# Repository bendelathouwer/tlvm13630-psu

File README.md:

# circuit explenation 

----------------------------------------------------------------------------------------------------------------------------------------

Now the input circuitry and output circuitry,   the input and output capasitors, the datasheet demands ceramic capasitors with a dielectricum of X7R or better.
Why ceramic capacitors you may ask? because there ESR(equivalent series resitance) is low. which in turn means  lower ripel , control loop is stabel, better transient response and the losses are lower.

For the output circuitry we especialy want that to be suuper stable , why you may ask? Let me show you.

As you can see from this block diagram of the chip  the feedback circuitry is connected (via resistors) to the output. So as you can guess and see any oscilation will upset the comperator which in turn will pass and upset the control circuitry

----------------------------------------------------------------------------------------------------------------------------------

Now we will explain the controll pins a bit.
The first pin we encounter is the Enable pin, which we can use in one of three ways/
The first way is to just tie it to the input voltage , when we do this the convertor will start working whenever a input voltage is present.
The next posibility is to connect an external signal to the enable pin , this can be a microcontroller for example or this can be the power good signal of a upstream convertor.
This is done for when powersequencing is needed , an example of power sequencing can be seen below.

The next and last posebility is to add a voltage devider so we enable the UVLO(Under Voltage Lock Out). This will disable the convertor until a certain voltage is reached or disable the convertor if a voltage dips below a treshold.
This is handy when we are using batterys for example 

The next pin will be the Rt pin ,this pin sets the internal oscilator via a resistor. We need to be careful to choose this resistor. The higher the frequency the more emc and efficency  will become a problem BUT the components can be smaller.
The lower the frequency the lower emc will be and the efficency will be higher BUT the components will be bigger 

The next pin is the VCC pin which comes from the external regulator. Now the datasheet mentions multiple times that there shoudn't be any load connected to the VCC pin BUT in the application schematic in the datasheet it show a load (albeit a pull up).
The EVM schematic shows no load even no pullup connected, so for me it is a mistery if you should or should not connect a load to it.

Next pin is the power good pin , this pin is an open drain pin. This pin will indicate if the convertor works as intended or not.
Also this pin can connect to the enable pin of a downstream converter. So to enable power sequencing as mentiond above.

---------------------------------------------------------------------------------------------------------------------------------------

So the final pin is the feedback pin with it's resistor diverder , this voltage divider will set the input voltage at the input of the controll circuit comperator.
The lower resistor is recomended at 10K and the upper can be a calculated value BUT be awere resistors larger than 1M can introduce noise which in turn will upset the controll circuitry.
Also the feedback trace needs to be short and and bee kept away to again reduce noise.

---------------------------------------------------------------------------------------------------------------------------------------

 # schematic details  
 
As you can see in the overview of the schematic I have a couple of DNP components, I think we all have been there we have our boards in our hands but then we realise some feature of the chip isn't brought out.
So after our little cry we have to spend extra money and time on a new board. So with the DNP parts we have already have a footprint there and so we can easly adapt and continue with a smile.
You will also notice I like to work with collors and net names , the reason behind that is realy simple. So I can see in a blink of an eye what net I am dealing with. This both in the layout side and schematic capture side of things.You will also notice formulas, tables and annotations. This is done so that I don't need to scroll trough the data sheet or have it open on the desktop. We all know engineers have limited desktop space.

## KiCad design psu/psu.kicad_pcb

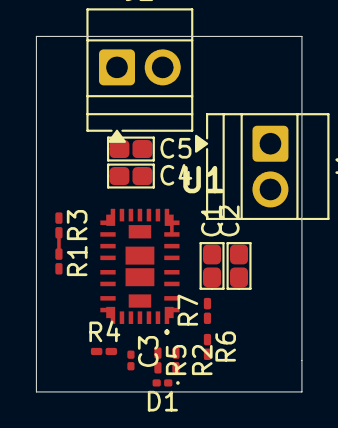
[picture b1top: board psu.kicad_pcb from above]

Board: 2 copper layers, 14.8 x 19.8 mm, 16 parts (0 on the bottom side), 10 nets.

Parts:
C1, C2, C4, C5: 4.7u; 0603
C3: 1u; C_0201_0603Metric
D1: LED_Small; LED_0201_0603Metric
J1, J2: Screw_Terminal_01x02; TerminalBlock_Xinya_XY308-2.54-2P_1x02_P2.54mm_Horizontal
R1: 10K; R_0201_0603Metric_Pad0.64x0.40mm_HandSolder
R2: 22K; R_0201_0603Metric_Pad0.64x0.40mm_HandSolder
R3: 34K; R_0201_0603Metric_Pad0.64x0.40mm_HandSolder
R4, R5, R6: R_0201_0603Metric_Pad0.64x0.40mm_HandSolder
R7: 0; R_0201_0603Metric_Pad0.64x0.40mm_HandSolder
U1: TLVM13630

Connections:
/EN: R6.1, R7.1, U1.2 (EN)
/FB: R1.1, R3.2, U1.25 (FB)
/PG: R4.1, R5.1, U1.26 (PG)
/RT: R2.2, U1.1 (RT)
/VCC: C3.1, R4.2, U1.23 (VCC)
/Vin: C1.1, C2.1, J1.2, R7.2, U1.3 (VIN), U1.4 (VIN), U1.18 (VIN), U1.19 (VIN)
/Vout: C4.1, C5.1, J2.1, R3.1, U1.7 (VOUT), U1.8 (VOUT), U1.9 (VOUT), U1.10 (VOUT), U1.12 (VOUT), U1.13 (VOUT), U1.14 (VOUT), U1.15 (VOUT)
AGND: R1.2, R2.1, R6.2, U1.24 (AGND)
unnamed: D1.2 (A), R5.2
PGND: C1.2, C2.2, C3.2, C4.2, C5.2, D1.1 (K), J1.1, J2.2, U1.5 (PGND), U1.6 (PGND), U1.16 (PGND), U1.17 (PGND)

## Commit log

2026-04-01 started
    started working on the psu project
2026-04-01 semi finished the schematic , next up anotation and PCB layout
2026-04-01 added bom and finished the schematic , board will be a pita
2026-04-01 made the pcb , It's a bit trash but still need to make a q&a document
2026-04-01 finished
    finished the schematic , bom and rough pcb outline
2026-04-02 cleaned up the repo
2026-04-02 Create q&a.md with design insights and images
    Added a new Q&A section with images and explanations for design choices.
2026-04-02 Update q&a.md with input circuitry information
    Added details about input circuitry and capacitor specifications.
2026-04-02 Fix grammar and spelling in Q&A about capacitors
    Corrected grammar and spelling errors in the explanation of input capacitors and their benefits.
2026-04-02 Fix formatting of schematic details header
2026-04-02 Rename README.md to intro.md
2026-04-02 update
    updated the readme
2026-04-02 Fix typos and enhance readability in README.md
    Correct typos and improve clarity in the README.
2026-04-02 Update README with feedback pin details
    Added information about the feedback pin in the README.
2026-04-02 Enhance README with images and formatting
    Added images and updated formatting in the README.
2026-04-02 Enhance README with DNP components explanation
    Added explanation about DNP components in schematic details.
2026-04-02 Fix typos in README schematic details section
    Corrected typos and improved clarity in the schematic details section.
2026-04-02 Fix typos and enhance readability in README
    Corrected typos and improved clarity in the README.
2026-04-02 Fix typos in README.md
2026-04-02 Fix typos and improve clarity in README
    Corrected spelling and grammatical errors in the README.
2026-04-02 Adjust positions in psu.kicad_sch and add backup
    Shifted coordinates for multiple schematic elements (text, image, power symbols, net-tie properties) to refine layout in psu.kicad_sch. Also added a backup archive psu/psu-backups/psu-2026-04-02_2009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
2026-04-02 Add image to README for better visualization
    Added an image to enhance the README content.
2026-04-02 Normalize BOM CSV; add backups and history gitignore
    Convert files/psu.csv from quoted comma-separated format to semicolon-separated and clean up price/field formatting for easier parsing. Add psu/.history/.gitignore to ignore fp-info-cache, *-backups 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
